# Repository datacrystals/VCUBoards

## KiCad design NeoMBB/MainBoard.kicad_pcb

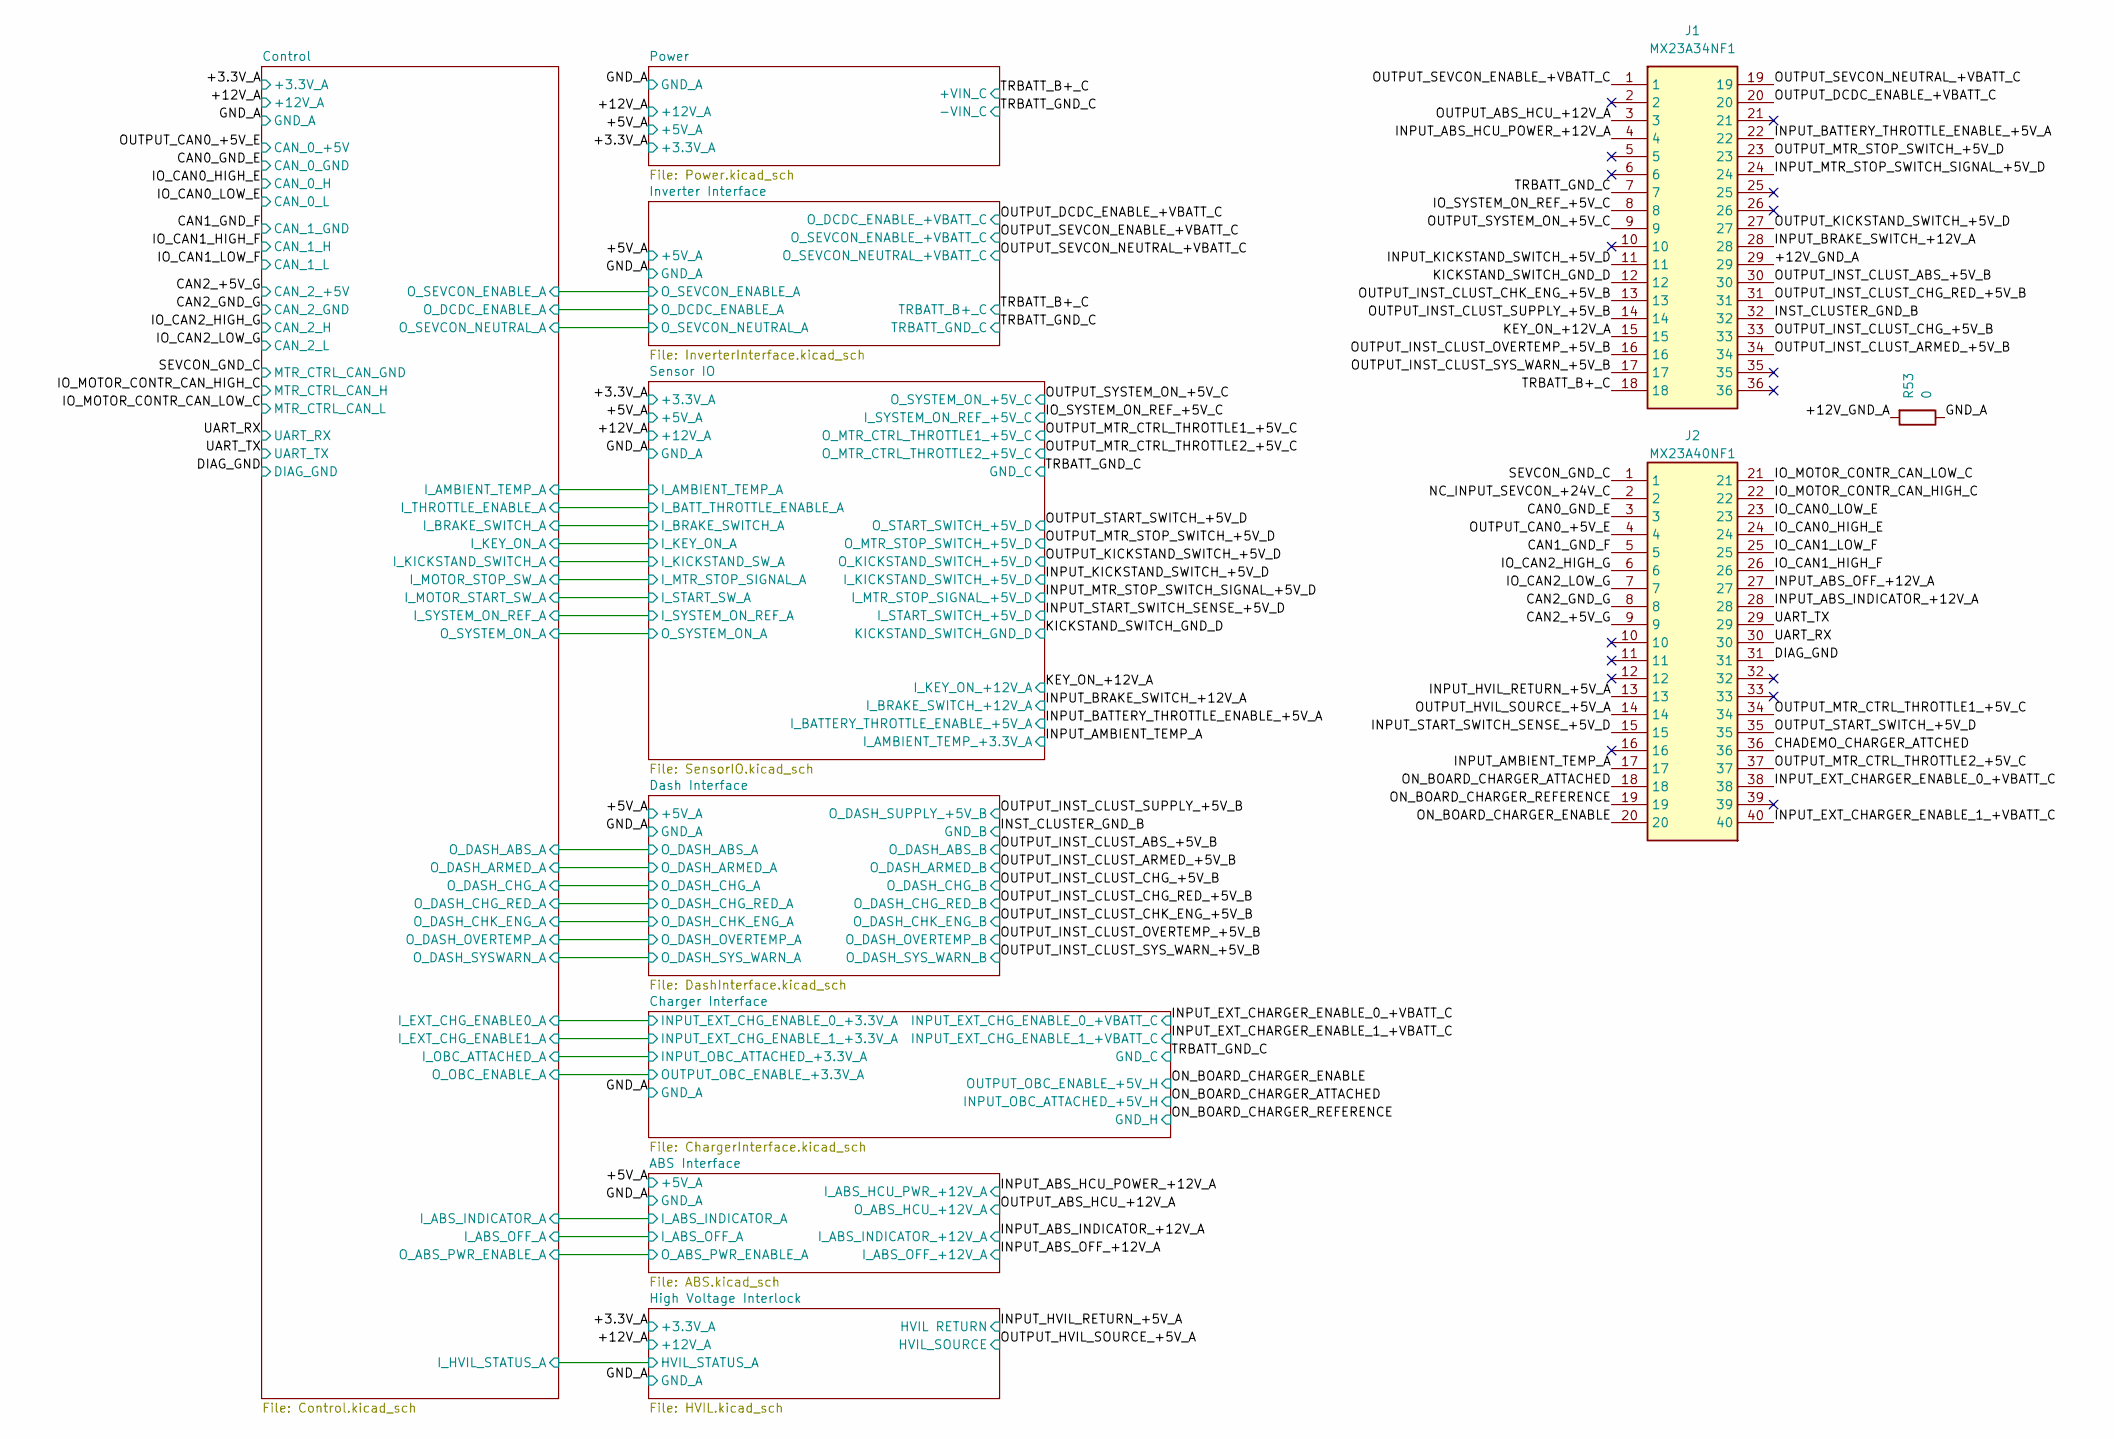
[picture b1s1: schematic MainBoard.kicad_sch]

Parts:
J1: MX23A34NF1; Mouser Part Number 656-MX23A34NF1
J2: MX23A40NF1; Mouser Part Number 656-MX23A40NF1
R53: 0; R_1210_3225Metric_Pad1.30x2.65mm_HandSolder

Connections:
/+12V_GND_A: J1.29, R53.2
/CAN0_GND_E: J2.3; also elsewhere on the board
/CAN1_GND_F: J2.5; also elsewhere on the board
/CAN2_+5V_G: J2.9; also elsewhere on the board
/CAN2_GND_G: J2.8; also elsewhere on the board
/CHADEMO_CHARGER_ATTCHED: J2.36
/DIAG_GND: J2.31, R53.1; also elsewhere on the board
/INPUT_ABS_HCU_POWER_+12V_A: J1.4; also elsewhere on the board
/INPUT_ABS_INDICATOR_+12V_A: J2.28; also elsewhere on the board
/INPUT_ABS_OFF_+12V_A: J2.27; also elsewhere on the board
/INPUT_AMBIENT_TEMP_A: J2.17; also elsewhere on the board
/INPUT_BATTERY_THROTTLE_ENABLE_+5V_A: J1.22; also elsewhere on the board
/INPUT_BRAKE_SWITCH_+12V_A: J1.28; also elsewhere on the board
/INPUT_EXT_CHARGER_ENABLE_0_+VBATT_C: J2.38; also elsewhere on the board
/INPUT_EXT_CHARGER_ENABLE_1_+VBATT_C: J2.40; also elsewhere on the board
/INPUT_HVIL_RETURN_+5V_A: J2.13; also elsewhere on the board
/INPUT_KICKSTAND_SWITCH_+5V_D: J1.11; also elsewhere on the board
/INPUT_MTR_STOP_SWITCH_SIGNAL_+5V_D: J1.24; also elsewhere on the board
/INPUT_START_SWITCH_SENSE_+5V_D: J2.15; also elsewhere on the board
/INST_CLUSTER_GND_B: J1.32; also elsewhere on the board
/IO_CAN0_HIGH_E: J2.24; also elsewhere on the board
/IO_CAN0_LOW_E: J2.23; also elsewhere on the board
/IO_CAN1_HIGH_F: J2.26; also elsewhere on the board
/IO_CAN1_LOW_F: J2.25; also elsewhere on the board
/IO_CAN2_HIGH_G: J2.6; also elsewhere on the board
/IO_CAN2_LOW_G: J2.7; also elsewhere on the board
/IO_MOTOR_CONTR_CAN_HIGH_C: J2.22; also elsewhere on the board
/IO_MOTOR_CONTR_CAN_LOW_C: J2.21; also elsewhere on the board
/IO_SYSTEM_ON_REF_+5V_C: J1.8; also elsewhere on the board
/KEY_ON_+12V_A: J1.15; also elsewhere on the board
/KICKSTAND_SWITCH_GND_D: J1.12; also elsewhere on the board
/NC_INPUT_SEVCON_+24V_C: J2.2
/ON_BOARD_CHARGER_ATTACHED: J2.18; also elsewhere on the board
/ON_BOARD_CHARGER_ENABLE: J2.20; also elsewhere on the board
/ON_BOARD_CHARGER_REFERENCE: J2.19; also elsewhere on the board
/OUTPUT_ABS_HCU_+12V_A: J1.3; also elsewhere on the board
/OUTPUT_CAN0_+5V_E: J2.4; also elsewhere on the board
/OUTPUT_DCDC_ENABLE_+VBATT_C: J1.20; also elsewhere on the board
/OUTPUT_HVIL_SOURCE_+5V_A: J2.14; also elsewhere on the board
/OUTPUT_INST_CLUST_ABS_+5V_B: J1.30; also elsewhere on the board
/OUTPUT_INST_CLUST_ARMED_+5V_B: J1.34; also elsewhere on the board
/OUTPUT_INST_CLUST_CHG_+5V_B: J1.33; also elsewhere on the board
/OUTPUT_INST_CLUST_CHG_RED_+5V_B: J1.31; also elsewhere on the board
/OUTPUT_INST_CLUST_CHK_ENG_+5V_B: J1.13; also elsewhere on the board
/OUTPUT_INST_CLUST_OVERTEMP_+5V_B: J1.16; also elsewhere on the board
/OUTPUT_INST_CLUST_SUPPLY_+5V_B: J1.14; also elsewhere on the board
/OUTPUT_INST_CLUST_SYS_WARN_+5V_B: J1.17; also elsewhere on the board
/OUTPUT_KICKSTAND_SWITCH_+5V_D: J1.27; also elsewhere on the board
/OUTPUT_MTR_CTRL_THROTTLE1_+5V_C: J1.9, J2.34, J2.37; also elsewhere on the board
/OUTPUT_MTR_STOP_SWITCH_+5V_D: J1.23; also elsewhere on the board
/OUTPUT_SEVCON_ENABLE_+VBATT_C: J1.1; also elsewhere on the board
/OUTPUT_SEVCON_NEUTRAL_+VBATT_C: J1.19; also elsewhere on the board
/OUTPUT_START_SWITCH_+5V_D: J2.35; also elsewhere on the board
/SEVCON_GND_C: J2.1; also elsewhere on the board
/TRBATT_B+_C: J1.18; also elsewhere on the board
/TRBATT_GND_C: J1.7; also elsewhere on the board
/UART_RX: J2.30; also elsewhere on the board
/UART_TX: J2.29; also elsewhere on the board

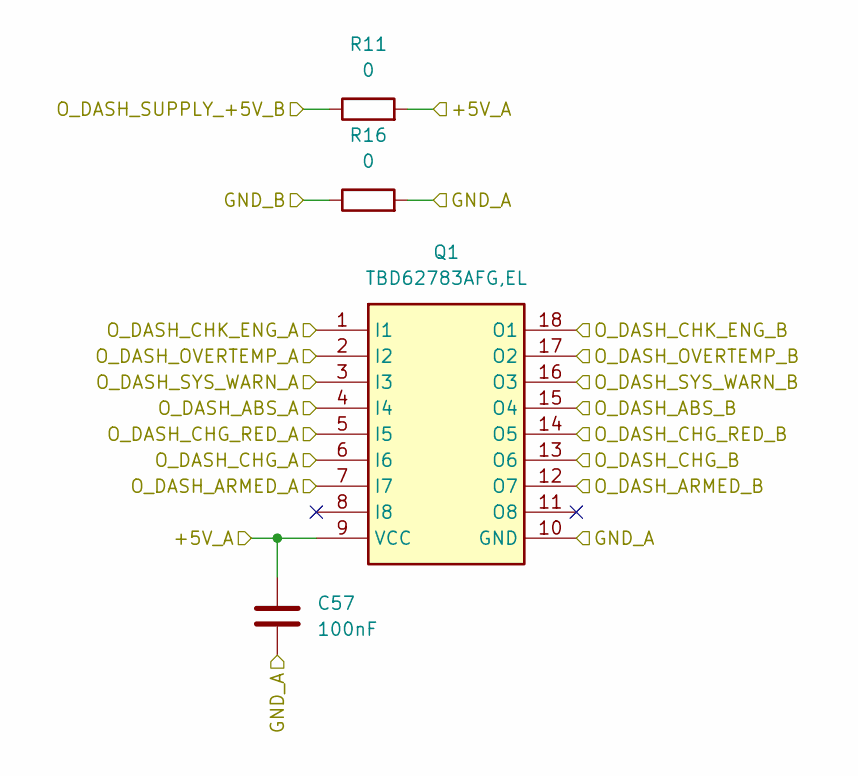
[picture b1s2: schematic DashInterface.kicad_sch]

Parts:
C57: 100nF; C_1210_3225Metric_Pad1.33x2.70mm_HandSolder
Q1: TBD62783AFG,EL; SOIC127P1030X245-18N; Mouser Part Number 757-TBD62783AFGEL
R11, R16: 0; R_1210_3225Metric_Pad1.30x2.65mm_HandSolder

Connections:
/+5V_A: C57.1, Q1.9 (VCC), R11.2; also elsewhere on the board
/Control/O_DASH_ABS_A: Q1.4 (I4); also elsewhere on the board
/Control/O_DASH_ARMED_A: Q1.7 (I7); also elsewhere on the board
/Control/O_DASH_CHG_A: Q1.6 (I6); also elsewhere on the board
/Control/O_DASH_CHG_RED_A: Q1.5 (I5); also elsewhere on the board
/Control/O_DASH_CHK_ENG_A: Q1.1 (I1); also elsewhere on the board
/Control/O_DASH_OVERTEMP_A: Q1.2 (I2); also elsewhere on the board
/Control/O_DASH_SYSWARN_A: Q1.3 (I3); also elsewhere on the board
/DIAG_GND: C57.2, Q1.10 (GND), R16.2; also elsewhere on the board
/INST_CLUSTER_GND_B: R16.1; also elsewhere on the board
/OUTPUT_INST_CLUST_ABS_+5V_B: Q1.15 (O4); also elsewhere on the board
/OUTPUT_INST_CLUST_ARMED_+5V_B: Q1.12 (O7); also elsewhere on the board
/OUTPUT_INST_CLUST_CHG_+5V_B: Q1.13 (O6); also elsewhere on the board
/OUTPUT_INST_CLUST_CHG_RED_+5V_B: Q1.14 (O5); also elsewhere on the board
/OUTPUT_INST_CLUST_CHK_ENG_+5V_B: Q1.18 (O1); also elsewhere on the board
/OUTPUT_INST_CLUST_OVERTEMP_+5V_B: Q1.17 (O2); also elsewhere on the board
/OUTPUT_INST_CLUST_SUPPLY_+5V_B: R11.1; also elsewhere on the board
/OUTPUT_INST_CLUST_SYS_WARN_+5V_B: Q1.16 (O3); also elsewhere on the board

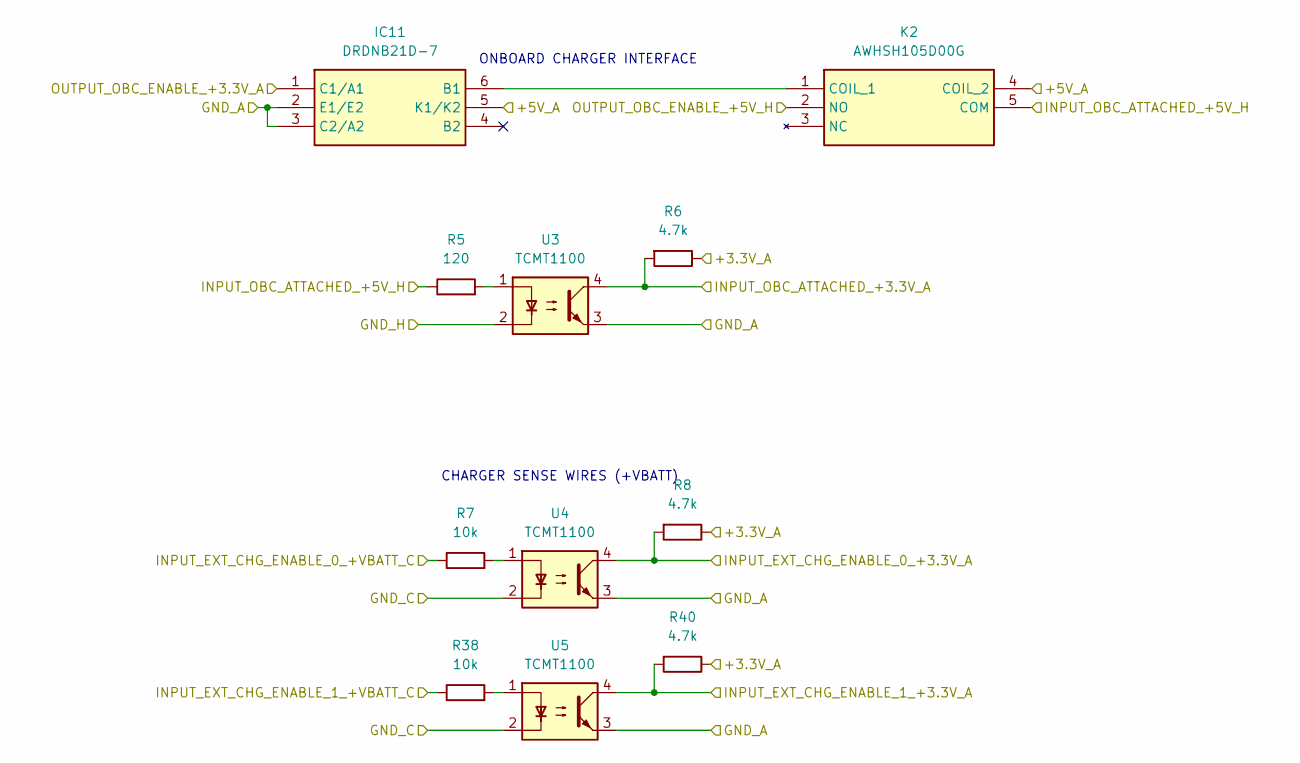
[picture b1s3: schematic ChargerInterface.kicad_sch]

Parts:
IC11: DRDNB21D-7; SOT65P210X110-6N; Mouser Part Number 621-DRDNB21D-7
K2: AWHSH105D00G; Mouser Part Number 523-AWHSH105D00G
R5: 120; R_1210_3225Metric_Pad1.30x2.65mm_HandSolder
R6, R8, R40: 4.7k; R_1210_3225Metric_Pad1.30x2.65mm_HandSolder
R7, R38: 10k; R_1210_3225Metric_Pad1.30x2.65mm_HandSolder
U3, U4, U5: TCMT1100; SOP-4_4.4x2.6mm_P1.27mm

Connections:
/Charger Interface/+3.3V_A: R6.1, R8.1, R40.1
/Charger Interface/+5V_A: IC11.5 (K1/K2), K2.4 (COIL_2)
/Charger Interface/INPUT_EXT_CHG_ENABLE_0_+3.3V_A: R8.2, U4.4; also elsewhere on the board
/Charger Interface/INPUT_EXT_CHG_ENABLE_1_+3.3V_A: R40.2, U5.4; also elsewhere on the board
/Charger Interface/INPUT_OBC_ATTACHED_+3.3V_A: R6.2, U3.4; also elsewhere on the board
/Charger Interface/OUTPUT_OBC_ENABLE_+3.3V_A: IC11.1 (C1/A1); also elsewhere on the board
/DIAG_GND: IC11.2 (E1/E2), IC11.3 (C2/A2), U3.3, U4.3, U5.3; also elsewhere on the board
/INPUT_EXT_CHARGER_ENABLE_0_+VBATT_C: R7.1; also elsewhere on the board
/INPUT_EXT_CHARGER_ENABLE_1_+VBATT_C: R38.1; also elsewhere on the board
/ON_BOARD_CHARGER_ATTACHED: K2.5 (COM), R5.1; also elsewhere on the board
/ON_BOARD_CHARGER_ENABLE: K2.2 (NO); also elsewhere on the board
/ON_BOARD_CHARGER_REFERENCE: U3.2; also elsewhere on the board
/TRBATT_GND_C: U4.2, U5.2; also elsewhere on the board
unnamed: IC11.6 (B1), K2.1 (COIL_1)
unnamed: R5.2, U3.1
unnamed: R7.2, U4.1
unnamed: R38.2, U5.1

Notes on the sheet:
ONBOARD CHARGER INTERFACE
CHARGER SENSE WIRES (+VBATT)

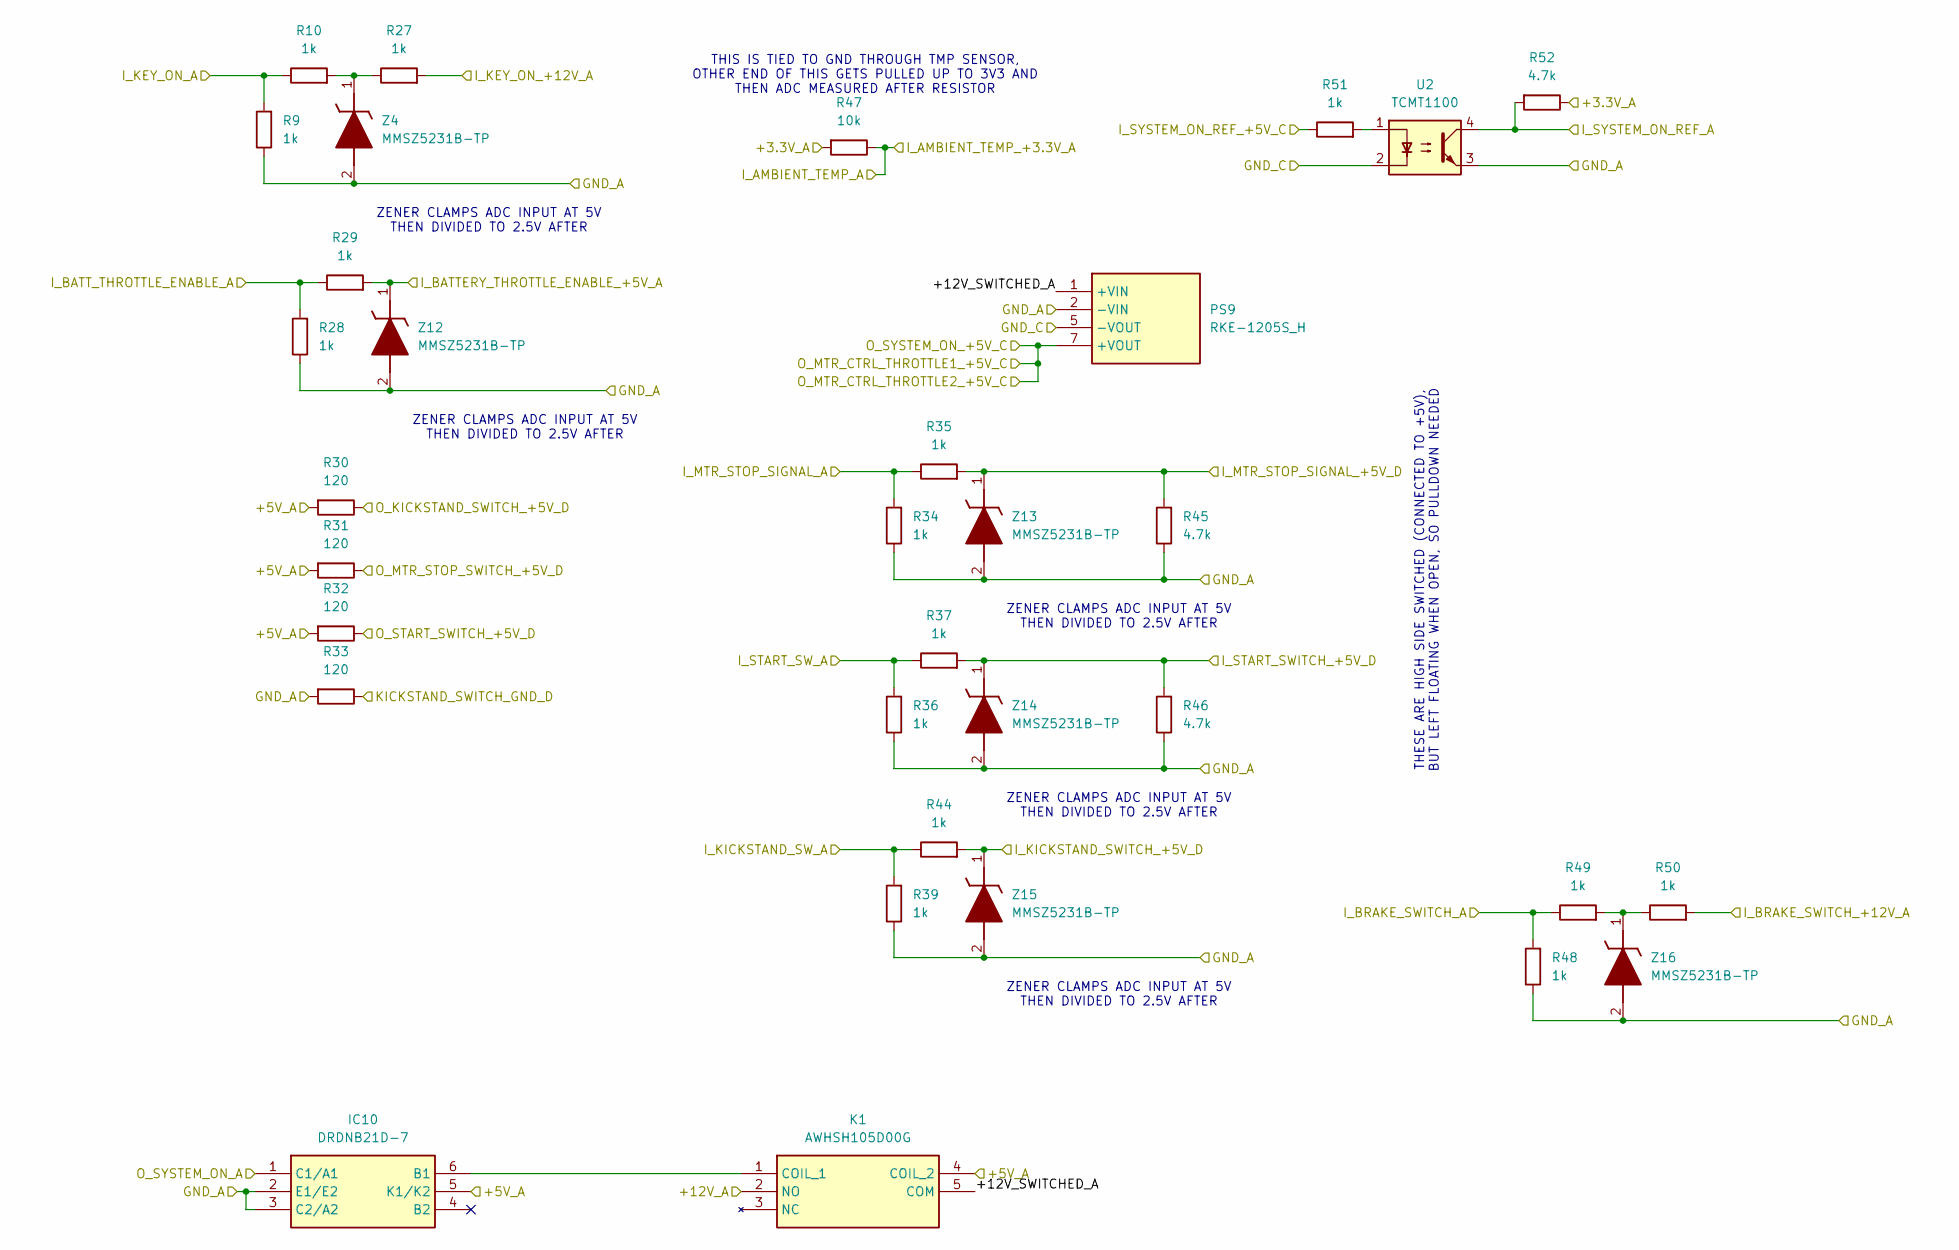
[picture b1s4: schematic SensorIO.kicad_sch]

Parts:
IC10: DRDNB21D-7; SOT65P210X110-6N; Mouser Part Number 621-DRDNB21D-7
K1: AWHSH105D00G; Mouser Part Number 523-AWHSH105D00G
PS9: RKE-1205S_H; RKE1205SH; Mouser Part Number 919-RKE-1205S/H
R9, R10, R27, R28, R29, R34, R35, R36, R37, R39, R44, R48, R49, R50, R51: 1k; R_1210_3225Metric_Pad1.30x2.65mm_HandSolder
R30, R31, R32, R33: 120; R_1210_3225Metric_Pad1.30x2.65mm_HandSolder
R45, R46, R52: 4.7k; R_1210_3225Metric_Pad1.30x2.65mm_HandSolder
R47: 10k; R_1210_3225Metric_Pad1.30x2.65mm_HandSolder
U2: TCMT1100; SOP-4_4.4x2.6mm_P1.27mm
Z4, Z12, Z13, Z14, Z15, Z16: MMSZ5231B-TP; SOD3716X135N; Mouser Part Number 833-MMSZ5231B-TP

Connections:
/+3.3V_A: R47.2, R52.1; also elsewhere on the board
/+5V_A: IC10.5 (K1/K2), K1.4 (COIL_2), R30.2, R31.2, R32.2; also elsewhere on the board
/+12V_A: K1.2 (NO); also elsewhere on the board
/Control/I_BRAKE_SWITCH_A: R48.2, R49.1; also elsewhere on the board
/Control/I_KEY_ON_A: R9.2, R10.1; also elsewhere on the board
/Control/I_KICKSTAND_SWITCH_A: R39.2, R44.1; also elsewhere on the board
/Control/I_MOTOR_START_SW_A: R36.2, R37.1; also elsewhere on the board
/Control/I_MOTOR_STOP_SW_A: R34.2, R35.1; also elsewhere on the board
/Control/I_SYSTEM_ON_REF_A: R52.2, U2.4; also elsewhere on the board
/Control/I_THROTTLE_ENABLE_A: R28.2, R29.1; also elsewhere on the board
/Control/O_SYSTEM_ON_A: IC10.1 (C1/A1); also elsewhere on the board
/DIAG_GND: IC10.2 (E1/E2), IC10.3 (C2/A2), PS9.2 (-VIN), R9.1, R28.1, R33.2, R34.1, R36.1, R39.1, R45.1, R46.1, R48.1, U2.3, Z4.2 (A), Z12.2 (A), Z13.2 (A), Z14.2 (A), Z15.2 (A), Z16.2 (A); also elsewhere on the board
/INPUT_AMBIENT_TEMP_A: R47.1; also elsewhere on the board
/INPUT_BATTERY_THROTTLE_ENABLE_+5V_A: R29.2, Z12.1 (K); also elsewhere on the board
/INPUT_BRAKE_SWITCH_+12V_A: R50.2; also elsewhere on the board
/INPUT_KICKSTAND_SWITCH_+5V_D: R44.2, Z15.1 (K); also elsewhere on the board
/INPUT_MTR_STOP_SWITCH_SIGNAL_+5V_D: R35.2, R45.2, Z13.1 (K); also elsewhere on the board
/INPUT_START_SWITCH_SENSE_+5V_D: R37.2, R46.2, Z14.1 (K); also elsewhere on the board
/IO_SYSTEM_ON_REF_+5V_C: R51.1; also elsewhere on the board
/KEY_ON_+12V_A: R27.2; also elsewhere on the board
/KICKSTAND_SWITCH_GND_D: R33.1; also elsewhere on the board
/OUTPUT_KICKSTAND_SWITCH_+5V_D: R30.1; also elsewhere on the board
/OUTPUT_MTR_CTRL_THROTTLE1_+5V_C: PS9.7 (+VOUT); also elsewhere on the board
/OUTPUT_MTR_STOP_SWITCH_+5V_D: R31.1; also elsewhere on the board
/OUTPUT_START_SWITCH_+5V_D: R32.1; also elsewhere on the board
/Sensor IO/+12V_SWITCHED_A: K1.5 (COM), PS9.1 (+VIN)
/TRBATT_GND_C: PS9.5 (-VOUT), U2.2; also elsewhere on the board
unnamed: IC10.6 (B1), K1.1 (COIL_1)
unnamed: R51.2, U2.1
unnamed: R10.2, R27.1, Z4.1 (K)
unnamed: R49.2, R50.1, Z16.1 (K)

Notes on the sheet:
ZENER CLAMPS ADC INPUT AT 5V THEN DIVIDED TO 2.5V AFTER
THESE ARE HIGH SIDE SWITCHED (CONNECTED TO +5V), BUT LEFT FLOATING WHEN OPEN, SO PULLDOWN NEEDED
THIS IS TIED TO GND THROUGH TMP SENSOR, OTHER END OF THIS GETS PULLED UP TO 3V3 AND THEN ADC MEASURED AFTER RESISTOR

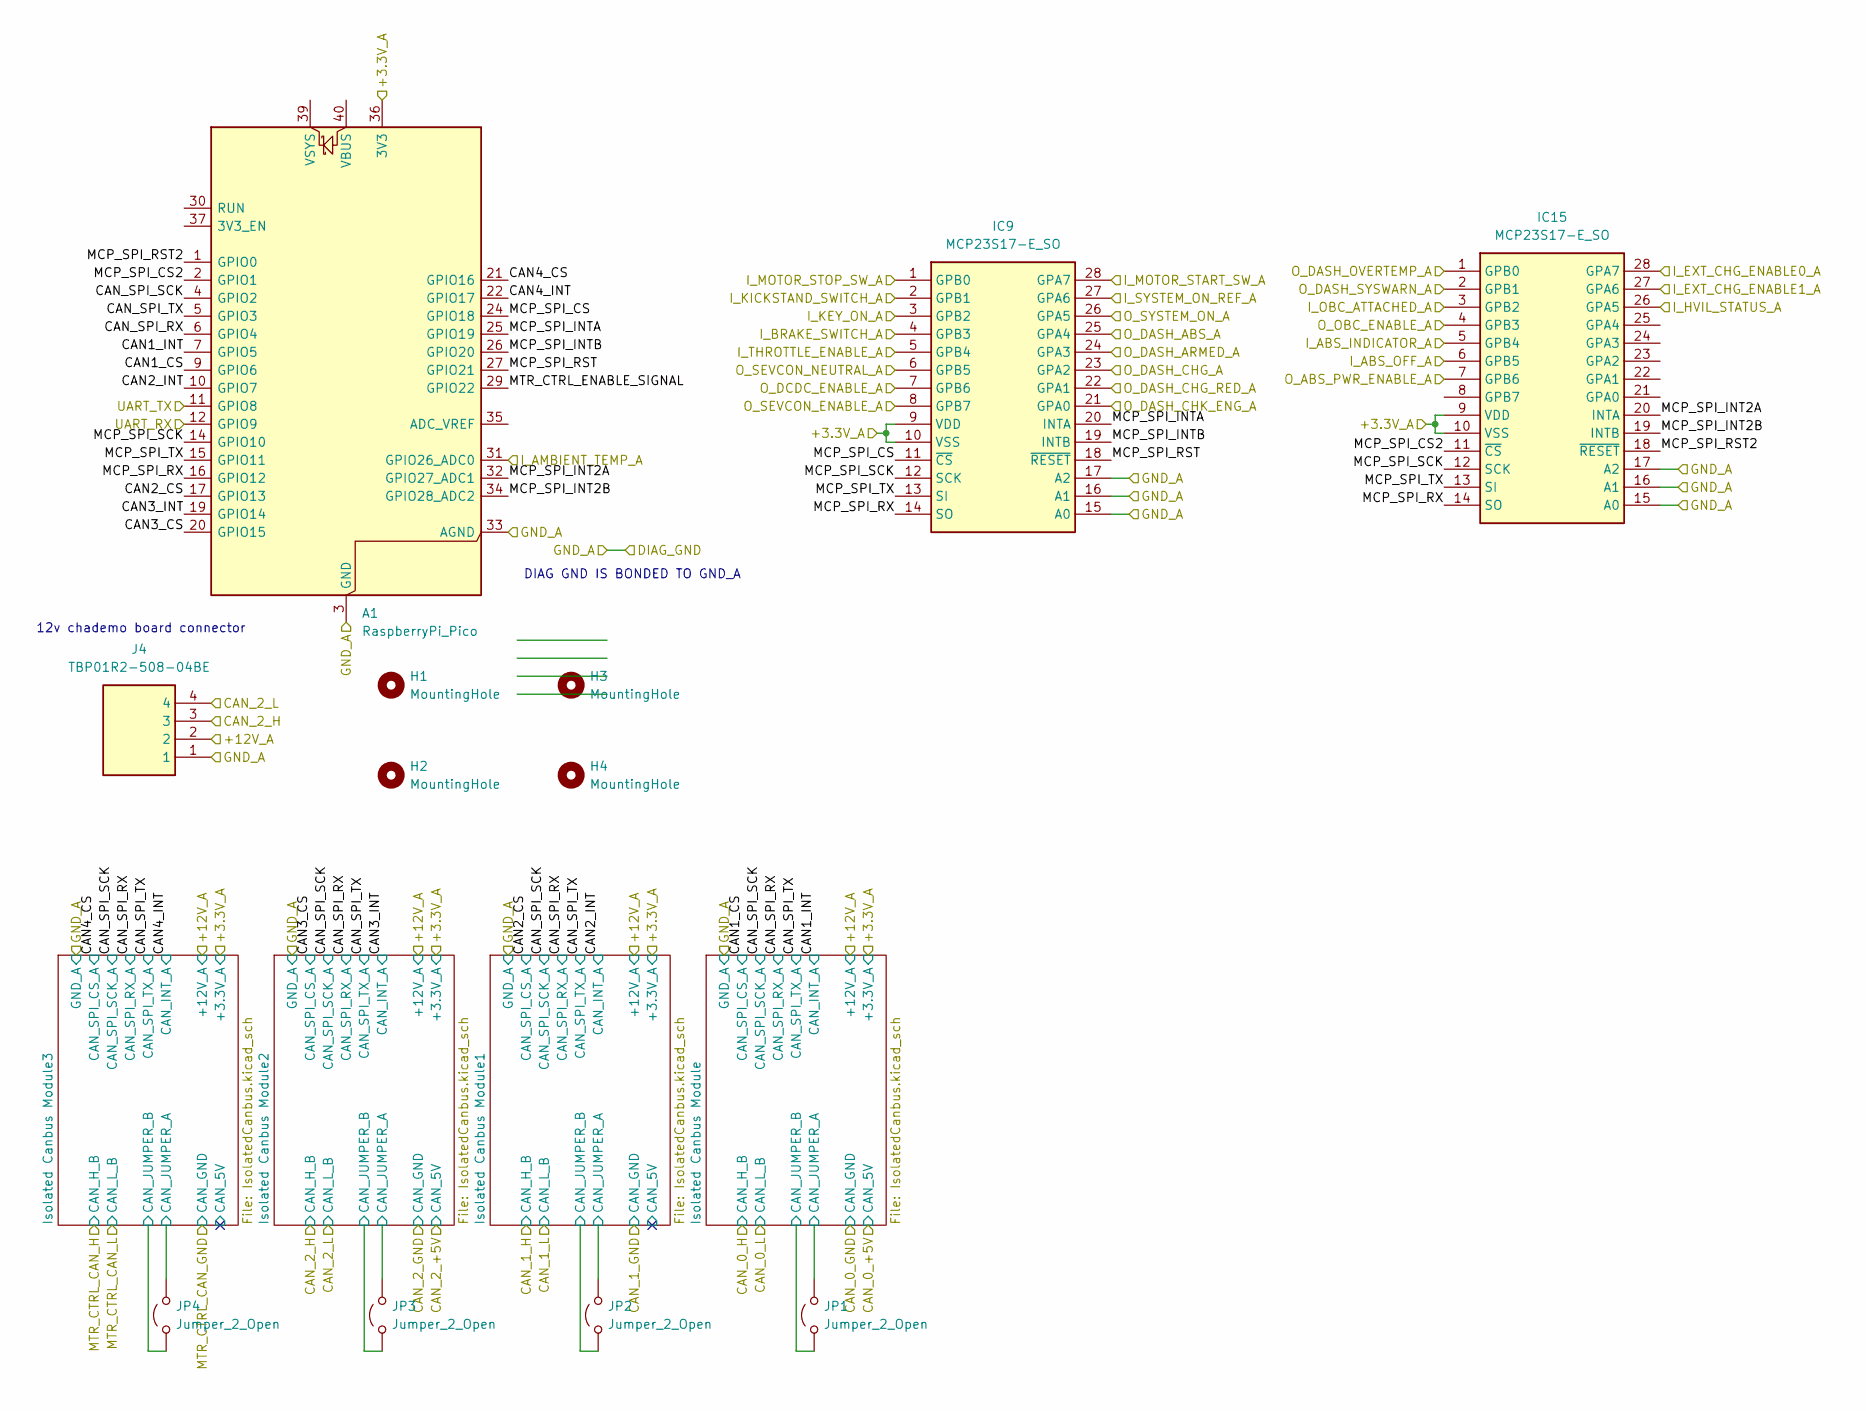
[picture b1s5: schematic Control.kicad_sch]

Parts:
A1: RaspberryPi_Pico; RaspberryPi_Pico_Common_THT
H1, H2, H3, H4: MountingHole; MountingHole_5.3mm_M5
IC9, IC15: MCP23S17-E_SO; SOIC127P1030X265-28N; Mouser Part Number 579-MCP23S17-E/SO
J4: TBP01R2-508-04BE; SHDR4W100P0X508_1X4_2192X850X1200P; Mouser Part Number 490-TBP01R2-508-04BE
JP1, JP2, JP3, JP4: Jumper_2_Open; SolderJumper-3_P2.0mm_Open_TrianglePad1.0x1.5mm

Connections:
/+3.3V_A: A1.36 (3V3), IC9.9 (VDD), IC9.10 (VSS), IC15.9 (VDD), IC15.10 (VSS); also elsewhere on the board
/+12V_A: J4.2; also elsewhere on the board
/ABS Interface/I_ABS_INDICATOR_A: IC15.5 (GPB4); also elsewhere on the board
/ABS Interface/I_ABS_OFF_A: IC15.6 (GPB5); also elsewhere on the board
/ABS Interface/O_ABS_PWR_ENABLE_A: IC15.7 (GPB6); also elsewhere on the board
/Charger Interface/INPUT_EXT_CHG_ENABLE_0_+3.3V_A: IC15.28 (GPA7); also elsewhere on the board
/Charger Interface/INPUT_EXT_CHG_ENABLE_1_+3.3V_A: IC15.27 (GPA6); also elsewhere on the board
/Charger Interface/INPUT_OBC_ATTACHED_+3.3V_A: IC15.3 (GPB2); also elsewhere on the board
/Charger Interface/OUTPUT_OBC_ENABLE_+3.3V_A: IC15.4 (GPB3); also elsewhere on the board
/Control/CAN1_CS: A1.9 (GPIO6); also elsewhere on the board
/Control/CAN1_INT: A1.7 (GPIO5); also elsewhere on the board
/Control/CAN2_CS: A1.17 (GPIO13); also elsewhere on the board
/Control/CAN2_INT: A1.10 (GPIO7); also elsewhere on the board
/Control/CAN3_CS: A1.20 (GPIO15); also elsewhere on the board
/Control/CAN3_INT: A1.19 (GPIO14); also elsewhere on the board
/Control/CAN4_CS: A1.21 (GPIO16); also elsewhere on the board
/Control/CAN4_INT: A1.22 (GPIO17); also elsewhere on the board
/Control/CAN_SPI_RX: A1.6 (GPIO4); also elsewhere on the board
/Control/CAN_SPI_SCK: A1.4 (GPIO2); also elsewhere on the board
/Control/CAN_SPI_TX: A1.5 (GPIO3); also elsewhere on the board
/Control/I_BRAKE_SWITCH_A: IC9.4 (GPB3); also elsewhere on the board
/Control/I_HVIL_STATUS_A: IC15.26 (GPA5); also elsewhere on the board
/Control/I_KEY_ON_A: IC9.3 (GPB2); also elsewhere on the board
/Control/I_KICKSTAND_SWITCH_A: IC9.2 (GPB1); also elsewhere on the board
/Control/I_MOTOR_START_SW_A: IC9.28 (GPA7); also elsewhere on the board
/Control/I_MOTOR_STOP_SW_A: IC9.1 (GPB0); also elsewhere on the board
/Control/I_SYSTEM_ON_REF_A: IC9.27 (GPA6); also elsewhere on the board
/Control/I_THROTTLE_ENABLE_A: IC9.5 (GPB4); also elsewhere on the board
/Control/Isolated Canbus Module1/CAN_JUMPER_B: JP2.1 (A); also elsewhere on the board
/Control/Isolated Canbus Module2/CAN_JUMPER_B: JP3.1 (A); also elsewhere on the board
/Control/Isolated Canbus Module3/CAN_JUMPER_B: JP4.1 (A); also elsewhere on the board
/Control/Isolated Canbus Module/CAN_JUMPER_B: JP1.1 (A); also elsewhere on the board
/Control/MCP_SPI_CS: A1.24 (GPIO18), IC9.11 (~CS)
/Control/MCP_SPI_CS2: A1.2 (GPIO1), IC15.11 (~CS)
/Control/MCP_SPI_INT2A: A1.32 (GPIO27_ADC1), IC15.20 (INTA)
/Control/MCP_SPI_INT2B: A1.34 (GPIO28_ADC2), IC15.19 (INTB)
/Control/MCP_SPI_INTA: A1.25 (GPIO19), IC9.20 (INTA)
/Control/MCP_SPI_INTB: A1.26 (GPIO20), IC9.19 (INTB)
/Control/MCP_SPI_RST: A1.27 (GPIO21), IC9.18 (~RESET)
/Control/MCP_SPI_RST2: A1.1 (GPIO0), IC15.18 (~RESET)
/Control/MCP_SPI_RX: A1.16 (GPIO12), IC9.14 (SO), IC15.14 (SO)
/Control/MCP_SPI_SCK: A1.14 (GPIO10), IC9.12 (SCK), IC15.12 (SCK)
/Control/MCP_SPI_TX: A1.15 (GPIO11), IC9.13 (SI), IC15.13 (SI)
/Control/MTR_CTRL_ENABLE_SIGNAL: A1.29 (GPIO22)
/Control/O_DASH_ABS_A: IC9.25 (GPA4); also elsewhere on the board
/Control/O_DASH_ARMED_A: IC9.24 (GPA3); also elsewhere on the board
/Control/O_DASH_CHG_A: IC9.23 (GPA2); also elsewhere on the board
/Control/O_DASH_CHG_RED_A: IC9.22 (GPA1); also elsewhere on the board
/Control/O_DASH_CHK_ENG_A: IC9.21 (GPA0); also elsewhere on the board
/Control/O_DASH_OVERTEMP_A: IC15.1 (GPB0); also elsewhere on the board
/Control/O_DASH_SYSWARN_A: IC15.2 (GPB1); also elsewhere on the board
/Control/O_DCDC_ENABLE_A: IC9.7 (GPB6); also elsewhere on the board
/Control/O_SEVCON_ENABLE_A: IC9.8 (GPB7); also elsewhere on the board
/Control/O_SEVCON_NEUTRAL_A: IC9.6 (GPB5); also elsewhere on the board
/Control/O_SYSTEM_ON_A: IC9.26 (GPA5); also elsewhere on the board
/DIAG_GND: A1.3 (GND), A1.8 (GND), A1.13 (GND), A1.18 (GND), A1.23 (GND), A1.28 (GND), A1.33 (AGND), A1.38 (GND), IC9.15 (A0), IC9.16 (A1), IC9.17 (A2), IC15.15 (A0), IC15.16 (A1), IC15.17 (A2), J4.1; also elsewhere on the board
/INPUT_AMBIENT_TEMP_A: A1.31 (GPIO26_ADC0); also elsewhere on the board
/IO_CAN0_HIGH_E: JP1.2 (B); also elsewhere on the board
/IO_CAN1_HIGH_F: JP2.2 (B); also elsewhere on the board
/IO_CAN2_HIGH_G: J4.3, JP3.2 (B); also elsewhere on the board
/IO_CAN2_LOW_G: J4.4; also elsewhere on the board
/IO_MOTOR_CONTR_CAN_HIGH_C: JP4.2 (B); also elsewhere on the board
/UART_RX: A1.12 (GPIO9); also elsewhere on the board
/UART_TX: A1.11 (GPIO8); also elsewhere on the board

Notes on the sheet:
DIAG GND IS BONDED TO GND_A
12v chademo board connector

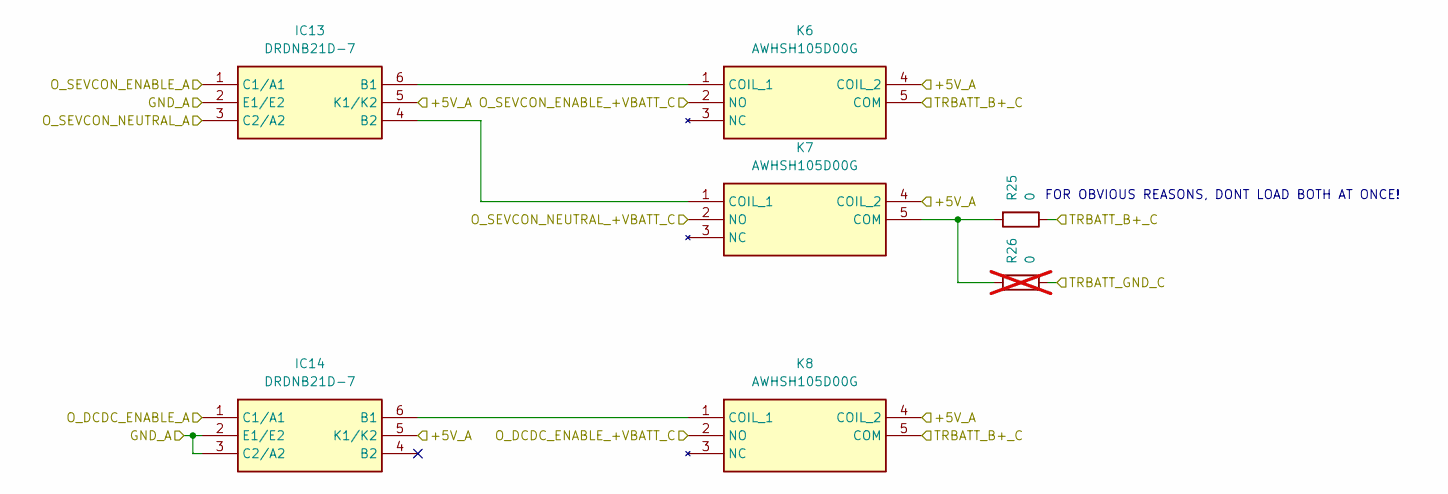
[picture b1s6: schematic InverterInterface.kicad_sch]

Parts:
IC13, IC14: DRDNB21D-7; SOT65P210X110-6N; Mouser Part Number 621-DRDNB21D-7
K6, K7, K8: AWHSH105D00G; Mouser Part Number 523-AWHSH105D00G
R25: 0; R_1210_3225Metric_Pad1.30x2.65mm_HandSolder
R26: 0; R_1210_3225Metric_Pad1.30x2.65mm_HandSolder; not fitted

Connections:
/+5V_A: IC13.5 (K1/K2), IC14.5 (K1/K2), K6.4 (COIL_2), K7.4 (COIL_2), K8.4 (COIL_2); also elsewhere on the board
/Control/O_DCDC_ENABLE_A: IC14.1 (C1/A1); also elsewhere on the board
/Control/O_SEVCON_ENABLE_A: IC13.1 (C1/A1); also elsewhere on the board
/Control/O_SEVCON_NEUTRAL_A: IC13.3 (C2/A2); also elsewhere on the board
/DIAG_GND: IC13.2 (E1/E2), IC14.2 (E1/E2), IC14.3 (C2/A2); also elsewhere on the board
/OUTPUT_DCDC_ENABLE_+VBATT_C: K8.2 (NO); also elsewhere on the board
/OUTPUT_SEVCON_ENABLE_+VBATT_C: K6.2 (NO); also elsewhere on the board
/OUTPUT_SEVCON_NEUTRAL_+VBATT_C: K7.2 (NO); also elsewhere on the board
/TRBATT_B+_C: K6.5 (COM), K8.5 (COM), R25.1; also elsewhere on the board
/TRBATT_GND_C: R26.1; also elsewhere on the board
unnamed: IC13.6 (B1), K6.1 (COIL_1)
unnamed: IC13.4 (B2), K7.1 (COIL_1)
unnamed: IC14.6 (B1), K8.1 (COIL_1)
unnamed: K7.5 (COM), R25.2, R26.2

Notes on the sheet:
FOR OBVIOUS REASONS, DONT LOAD BOTH AT ONCE!

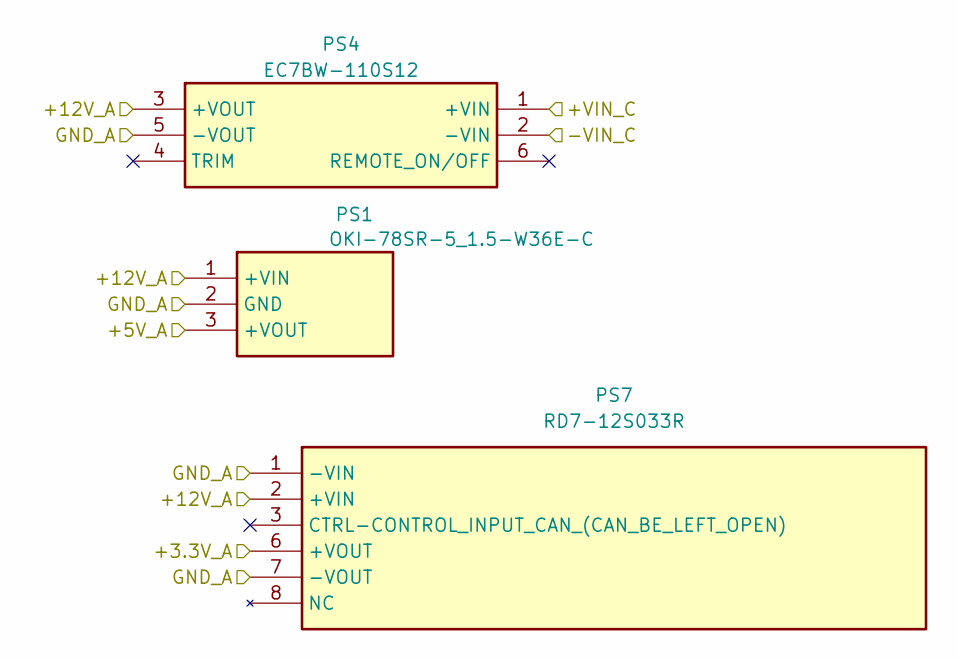
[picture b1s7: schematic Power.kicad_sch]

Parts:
PS1: OKI-78SR-5_1.5-W36E-C; OKI78SR515W36EC; Mouser Part Number 580-OK78SR5/1.5W36EC
PS4: EC7BW-110S12; EC7BW110S12; Mouser Part Number 418-EC7BW-110S12
PS7: RD7-12S033R; RD712S033R; Manufacturer_Part_Number RD7-12S033R

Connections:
/+3.3V_A: PS7.6 (+VOUT); also elsewhere on the board
/+5V_A: PS1.3 (+VOUT); also elsewhere on the board
/+12V_A: PS1.1 (+VIN), PS4.3 (+VOUT), PS7.2 (+VIN); also elsewhere on the board
/DIAG_GND: PS1.2 (GND), PS4.5 (-VOUT), PS7.1 (-VIN), PS7.7 (-VOUT); also elsewhere on the board
/TRBATT_B+_C: PS4.1 (+VIN); also elsewhere on the board
/TRBATT_GND_C: PS4.2 (-VIN); also elsewhere on the board

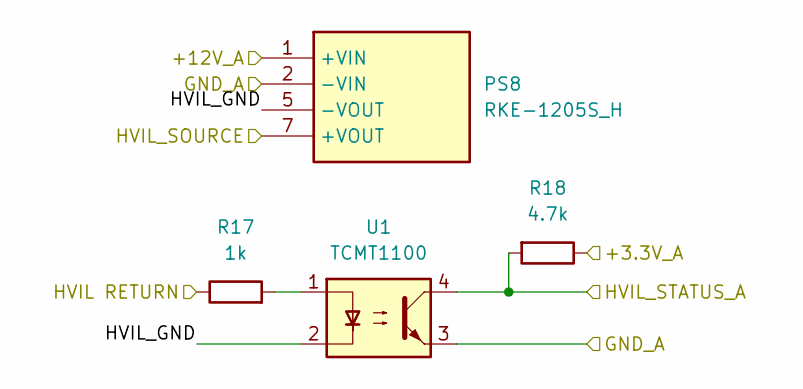
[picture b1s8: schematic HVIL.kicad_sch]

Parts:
PS8: RKE-1205S_H; RKE1205SH; Mouser Part Number 919-RKE-1205S/H
R17: 1k; R_1210_3225Metric_Pad1.30x2.65mm_HandSolder
R18: 4.7k; R_1210_3225Metric_Pad1.30x2.65mm_HandSolder
U1: TCMT1100; SOP-4_4.4x2.6mm_P1.27mm

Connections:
/+3.3V_A: R18.1; also elsewhere on the board
/+12V_A: PS8.1 (+VIN); also elsewhere on the board
/Control/I_HVIL_STATUS_A: R18.2, U1.4; also elsewhere on the board
/DIAG_GND: PS8.2 (-VIN), U1.3; also elsewhere on the board
/High Voltage Interlock/HVIL_GND: PS8.5 (-VOUT), U1.2
/INPUT_HVIL_RETURN_+5V_A: R17.1; also elsewhere on the board
/OUTPUT_HVIL_SOURCE_+5V_A: PS8.7 (+VOUT); also elsewhere on the board
unnamed: R17.2, U1.1

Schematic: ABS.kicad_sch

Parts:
IC12: DRDNB21D-7; SOT65P210X110-6N; Mouser Part Number 621-DRDNB21D-7
K5: AWHSH105D00G; Mouser Part Number 523-AWHSH105D00G
R19, R20, R21, R22, R23, R24: 1k; R_1210_3225Metric_Pad1.30x2.65mm_HandSolder
Z1, Z3: MMSZ5231B-TP; SOD3716X135N; Mouser Part Number 833-MMSZ5231B-TP

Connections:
/+5V_A: IC12.5 (K1/K2), K5.4 (COIL_2); also elsewhere on the board
/ABS Interface/I_ABS_INDICATOR_A: R19.2, R20.1; also elsewhere on the board
/ABS Interface/I_ABS_OFF_A: R22.2, R23.1; also elsewhere on the board
/ABS Interface/O_ABS_PWR_ENABLE_A: IC12.1 (C1/A1); also elsewhere on the board
/DIAG_GND: IC12.2 (E1/E2), R19.1, R22.1, Z1.2 (A), Z3.2 (A); also elsewhere on the board
/INPUT_ABS_HCU_POWER_+12V_A: K5.5 (COM); also elsewhere on the board
/INPUT_ABS_INDICATOR_+12V_A: R24.2; also elsewhere on the board
/INPUT_ABS_OFF_+12V_A: R21.2; also elsewhere on the board
/OUTPUT_ABS_HCU_+12V_A: K5.2 (NO); also elsewhere on the board
unnamed: IC12.6 (B1), K5.1 (COIL_1)
unnamed: R21.1, R23.2, Z1.1 (K)
unnamed: R20.2, R24.1, Z3.1 (K)

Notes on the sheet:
ZENER CLAMPS ADC INPUT AT 5V THEN DIVIDED TO 2.5V AFTER
